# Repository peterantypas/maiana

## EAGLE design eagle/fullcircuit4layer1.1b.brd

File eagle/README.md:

# Eagle CAD files

The new design is a single, 4-layer PCB which does not follow the conventional 4-Layer design paradigm.

- Layer 1 is the component and main signal layer as you might expect.
- Layer 2 is a power and signal layer with no ground pour. The only requirement is that these signals don't cross the RF path anywhere.
- Layer 3 is the ground layer. It is 100% uninterrupted save for via holes. RF traces on Layer 1 form coplanar waveguides with Layer 3 as ground.
- Layer 4 is yet another signal layer with ground pour. Because it lies underneath the ground its traces can go anywhere with no consequences.

By increasing the distance between the signal and ground layer, I was able to use very wide coplanar waveguide traces so as to minimize losses and parasitic inductance.
SWR is better than 1.1:1 with a 50 Ohm load.

The board now requires 7.5 Volts (because of the RF MOSFET). It draws 100 mA while receiving, and spikes to 680 mA during transmission at full power.
Surge current for transmission can be provided by a low-profile 10 mF supercapacitor on the back of the PCB. Also, during transmission,
the external LNA is powered down as a precaution.

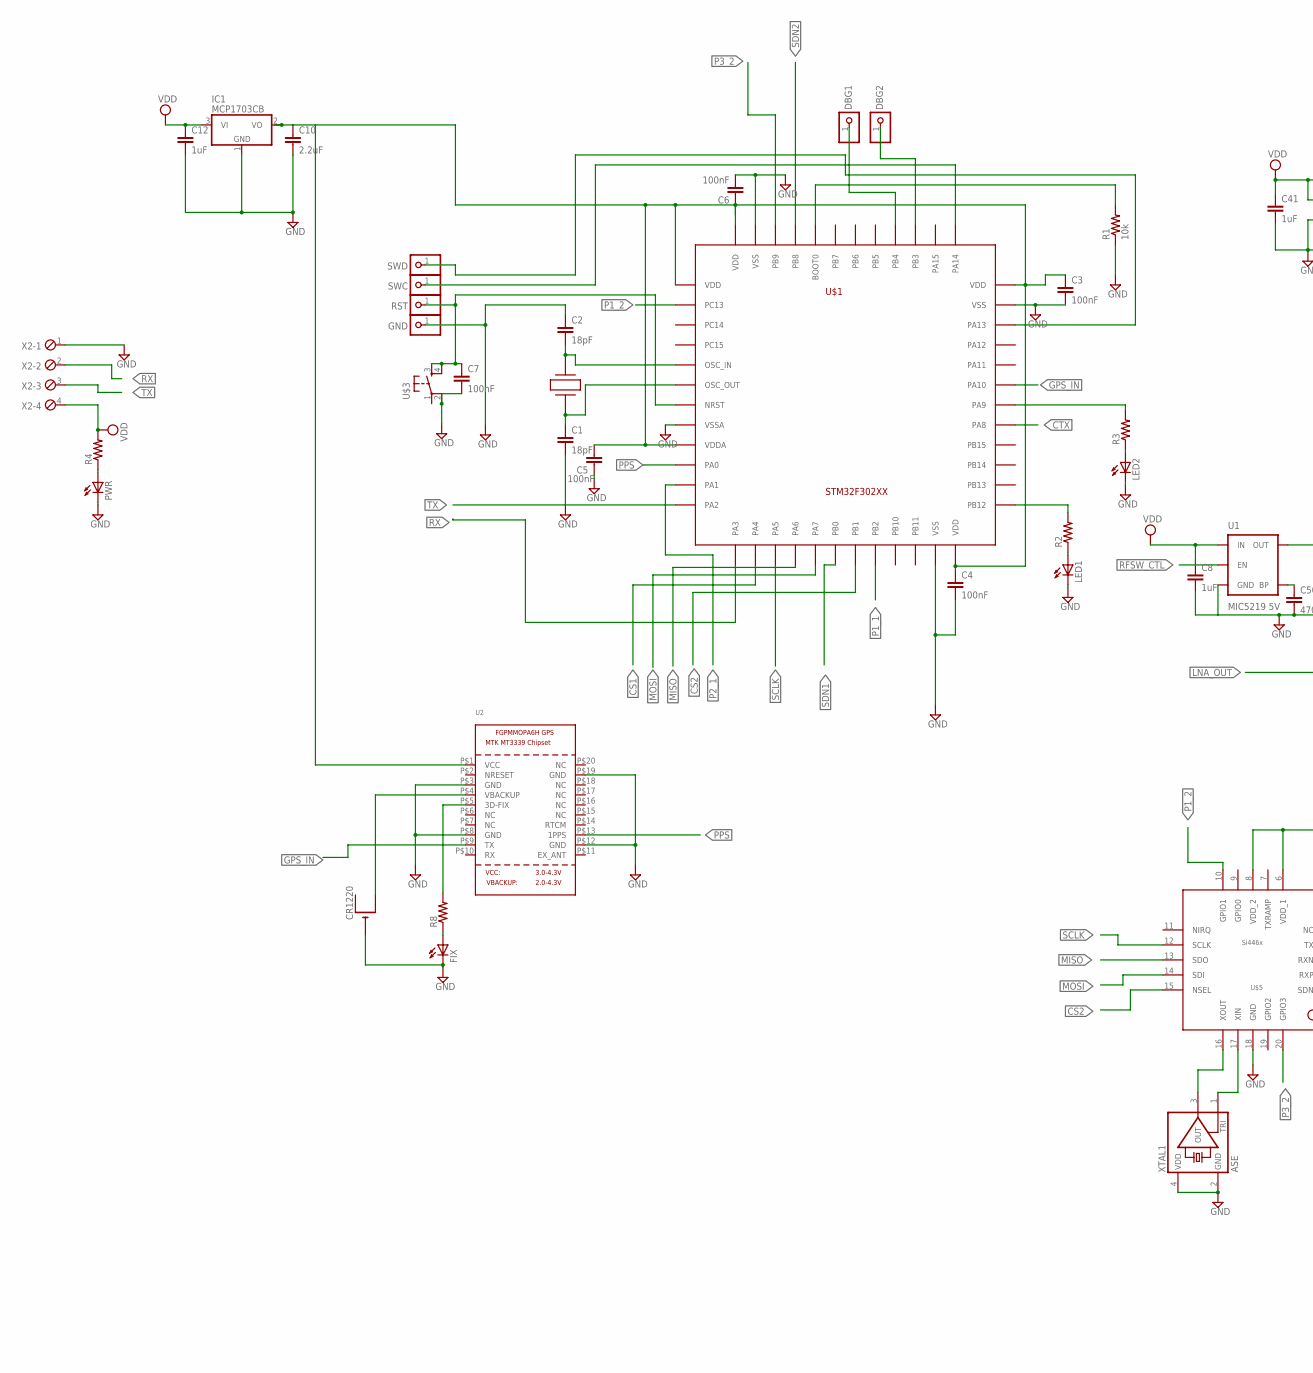
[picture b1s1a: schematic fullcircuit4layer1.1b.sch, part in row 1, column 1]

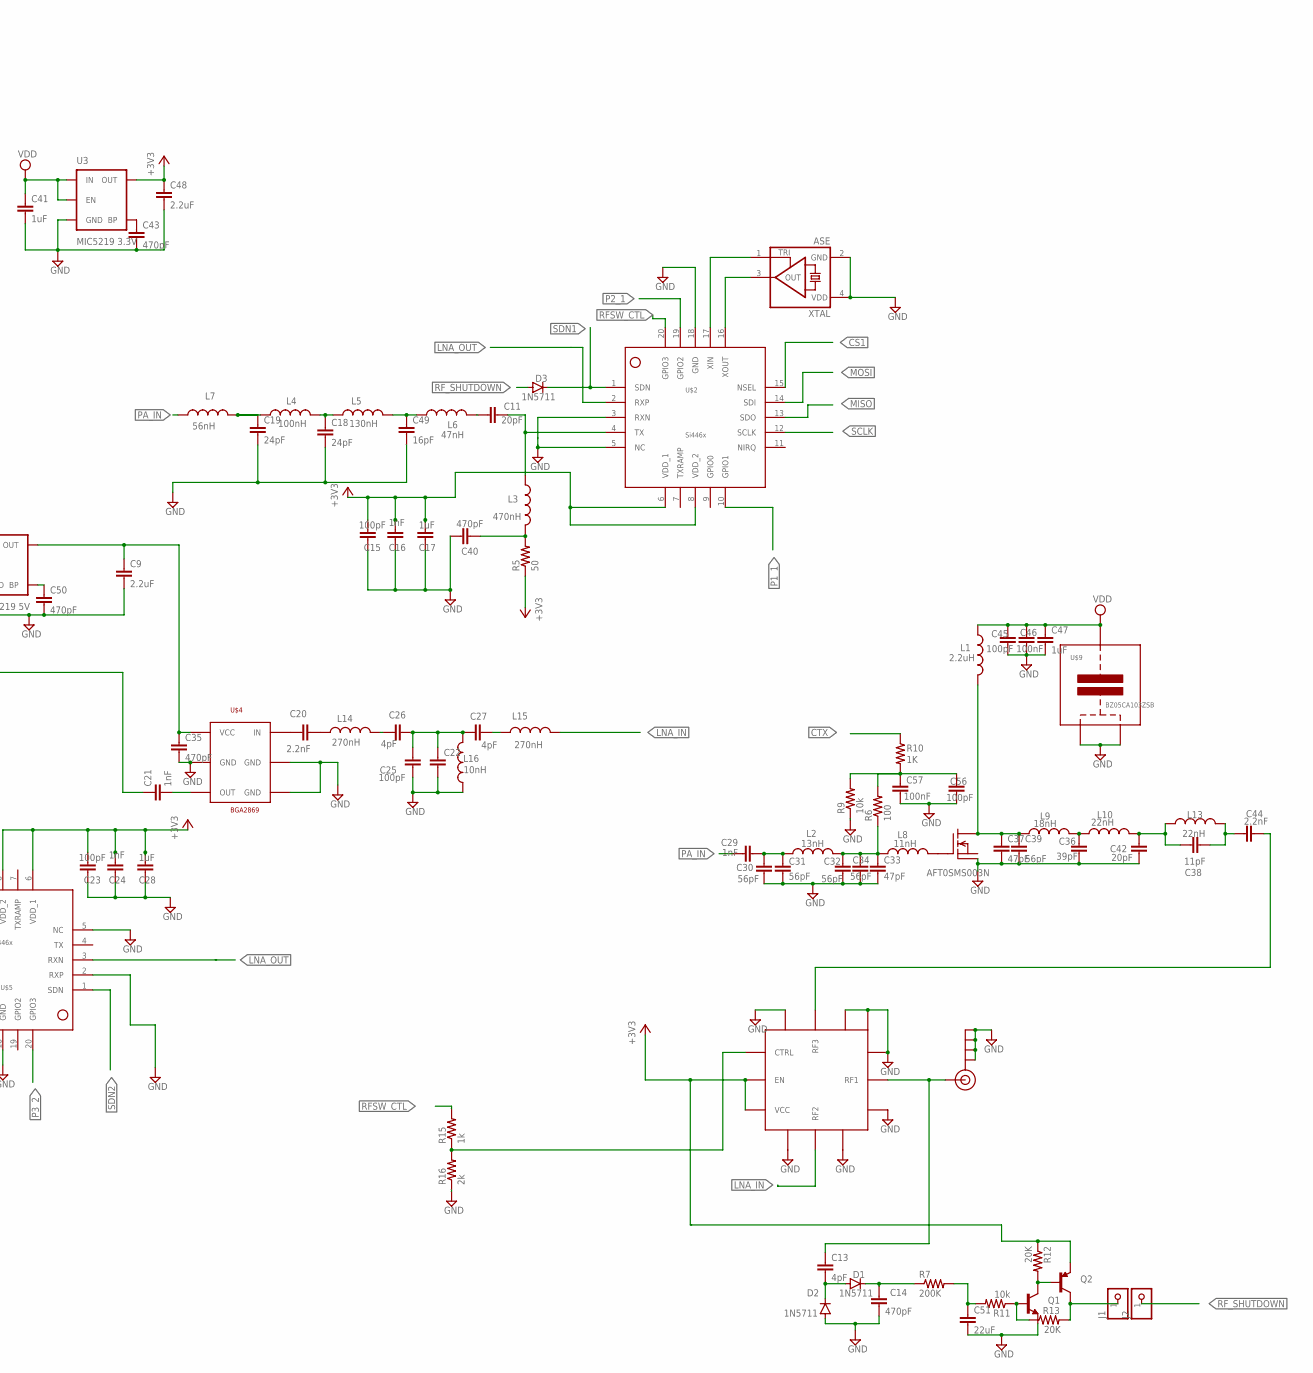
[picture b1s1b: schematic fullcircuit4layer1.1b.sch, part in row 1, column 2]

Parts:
C1, C2: 18pF; 0603-CAP
C3, C4, C5, C6, C7, C57: 100nF; 0603-CAP
C8, C12, C17, C28, C41: 1uF; 0603-CAP
C9, C48: 2.2uF; 0603-CAP
C10: 2.2uF; 0805
C11: 20pF; 0603-CAP
C13, C26, C27: 4pF; 0603-CAP
C14, C35, C40, C43, C50: 470pF; 0603-CAP
C15, C23, C25, C56: 100pF; 0603-CAP
C16, C24: 1nF; 0603-CAP
C18, C19: 24pF; 0603-CAP
C20, C44: 2.2nF; 0805
C21, C29: 1nF; 0805
C22: CAP0603-CAP; 0603-CAP
C30, C31, C32, C34: 56pF; 0603-CAP
C33: 47pF; 0603-CAP
C36: 39pF; 0805
C37: 47pF; 0805
C38: 11pF; 0805
C39: 56pF; 0805
C42: 20pF; 0805
C45: 100pF; 0805
C46: 100nF; 0805
C47: 1uF; 0805
C49: 16pF; 0603-CAP
C51: 22uF; 0805
CR1220: CR1220SMT; CR1220-SMD
D1, D2, D3: 1N5711; SOD-123
DBG1, DBG2: PINHD-1X1; 1X01
FIX: LEDCHIP-LED0603; CHIP-LED0603
GND: PINHD-1X1; 1X01
IC1: MCP1703CB; SOT23
J1, J2: PINHD-1X1; 1X01
J$1: SMA_EDGE; SMA-EDGE
L1: 2.2uH; 0805
L2: 13nH; 0603
L3: 470nH; 0805
L4: 100nH; 0603
L5: 130nH; 0603
L6: 47nH; 0603
L7: 56nH; 0603
L8: 11nH; 0603
L9: 18nH; 0805
L10, L13: 22nH; 0805
L14, L15: 270nH; 0603
L16: 10nH; 0603
LED1, LED2: LEDCHIP-LED0603; CHIP-LED0603
PWR: LEDCHIP-LED0603; CHIP-LED0603
Q1: TRANSISTOR_NPNSOT23-3; SOT23-3
Q2: TRANSISTOR_PNPSMD; SOT23-3
R1, R9, R11: 10k; 0603-RES
R2, R3, R4, R8: RESISTOR0603-RES; 0603-RES
R5: 50; 0603-RES
R6: 100; 0603-RES
R7: 200K; 0603-RES
R10: 1K; 0603-RES
R12, R13: 20K; 0603-RES
R15: 1k; 0603-RES
R16: 2k; 0603-RES
RST: PINHD-1X1; 1X01
SWC: PINHD-1X1; 1X01
SWD: PINHD-1X1; 1X01
U1: MIC5219 5V; SOT23-5
U2: GPS_FGPMMOPA6H; FGPMMOPA6H
U3: MIC5219 3.3V; SOT23-5
U$1: STM32F302XX; LQFP48
U$2, U$5: SI4463
U$3: TACTILE-SWITCH-7914G; 7914G
U$4: BGA2869; SOT363
U$6: SKYWORKS-13330397LF; QFN12
U$7: AFT0SMS003N; SOT-89
U$9: BZ05CA103ZSB; BZ05
X1: TXC_7A
X2: MPT4; 4POL254
XTAL, XTAL1: ASE

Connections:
+3V3: C15.1, C16.1, C17.1, C23.1, C24.1, C28.1, C48.1, Q2.2 (E), R5.1, R12.1, U3.5 (OUT), U$2.6 (VDD_1), U$2.8 (VDD_2), U$5.6 (VDD_1), U$5.8 (VDD_2), U$6.P$8 (EN), U$6.P$9 (VCC)
ANT: C13.1, J$1.SIG (SIGNAL), U$6.P$2 (RF1)
CS1: U$1.P$14 (PA4), U$2.15 (NSEL)
CS2: U$1.P$19 (PB1), U$5.15 (NSEL)
CTX: R10.1, U$1.P$29 (PA8)
GND: C1.2, C2.1, C3.2, C4.2, C5.1, C6.2, C7.2, C8.2, C9.2, C10.2, C12.2, C14.2, C15.2, C16.2, C17.2, C18.2, C19.2, C22.2, C23.2, C24.2, C25.1, C28.2, C30.2, C31.2, C32.2, C33.2, C34.2, C35.2, C36.2, C37.2, C39.2, C40.2, C41.2, C42.2, C43.2, C45.2, C46.2, C47.2, C48.2, C49.2, C50.2, C51.2, C56.2, C57.2, CR1220.-, D2.A, FIX.C, GND.1, IC1.1 (GND), J$1.GND@0 (GND), J$1.GND@1 (GND), J$1.GND@2 (GND), J$1.GND@3 (GND), L16.1, LED1.C, LED2.C, PWR.C, Q1.2 (E), R1.1, R9.1, R16.1, U1.2 (GND), U2.P$3 (GND), U2.P$8 (GND), U2.P$12 (GND), U2.P$19 (GND), U3.2 (GND), U$1.P$8 (VSSA), U$1.P$23 (VSS), U$1.P$35 (VSS), U$1.P$47 (VSS), U$2.3 (RXN), U$2.5 (NC), U$2.18 (GND), U$3.2, U$4.2 (GND), U$4.4 (GND), U$4.5 (GND), U$5.2 (RXP), U$5.5 (NC), U$5.18 (GND), U$6.P$1 (GND), U$6.P$3 (GND), U$6.P$4 (GND), U$6.P$6 (GND), U$6.P$10 (GND), U$6.P$12 (GND), U$7.2@1 (PAD), U$9.P$1, U$9.P$2, X2.1, XTAL.2 (GND), XTAL.4 (VDD), XTAL1.2 (GND), XTAL1.4 (VDD)
GPS_IN: U2.P$9 (TX), U$1.P$31 (PA10)
LNAPWR: C9.1, C35.1, U1.5 (OUT), U$4.1 (VCC)
LNA_IN: L15.2, U$6.P$11 (RF2)
LNA_OUT: C21.1, U$2.2 (RXP), U$5.3 (RXN)
MISO: U$1.P$16 (PA6), U$2.13 (SDO), U$5.13 (SDO)
MOSI: U$1.P$17 (PA7), U$2.14 (SDI), U$5.14 (SDI)
unnamed: U$2.17 (XIN), XTAL.1 (TRI)
unnamed: C19.1, L4.1, L7.2
unnamed: C18.1, L4.2, L5.1
unnamed: R1.2, U$1.P$44 (BOOT0)
unnamed: SWC.1, U$1.P$37 (PA14)
unnamed: R2.2, U$1.P$25 (PB12)
unnamed: SWD.1, U$1.P$34 (PA13)
unnamed: C11.1, L3.1, U$2.4 (TX)
unnamed: C2.2, U$1.P$5 (OSC_IN), X1.P$2
unnamed: C20.1, U$4.6 (IN)
unnamed: C21.2, U$4.3 (OUT)
unnamed: FIX.A, R8.1
unnamed: U$2.16 (XOUT), XTAL.3 (OUT)
unnamed: LED1.A, R2.1
unnamed: C20.2, L14.1
unnamed: LED2.A, R3.1
unnamed: R3.2, U$1.P$30 (PA9)
unnamed: C1.1, U$1.P$6 (OSC_OUT), X1.P$1
unnamed: PWR.A, R4.1
unnamed: C49.1, L5.2, L6.1
unnamed: DBG2.1, U$1.P$39 (PB3)
unnamed: C3.1, C4.1, C5.2, C6.1, C10.1, IC1.2 (VO), U2.P$1 (VCC), U$1.P$1 (VDD), U$1.P$9 (VDDA), U$1.P$24 (VDD), U$1.P$36 (VDD), U$1.P$48 (VDD)
unnamed: C37.1, C39.1, L1.2, L9.1, U$7.3 (D)
unnamed: DBG1.1, U$1.P$40 (PB4)
unnamed: L8.2, U$7.1 (G)
unnamed: C32.1, C33.1, C34.1, L2.2, L8.1, R6.1
unnamed: C29.2, C30.1, C31.1, L2.1
unnamed: C36.1, L9.2, L10.1
unnamed: C38.1, C42.1, L10.2, L13.1
unnamed: R8.2, U2.P$5 (3D-FIX)
unnamed: C43.1, U3.4 (BP)
unnamed: C13.2, D1.A, D2.C
unnamed: CR1220.+$2 (+1), U2.P$4 (VBACKUP)
unnamed: C22.1, C25.2, C26.1, C27.2, L16.2
unnamed: C27.1, L15.1
unnamed: C26.2, L14.2
unnamed: C50.1, U1.4 (BP)
unnamed: U$5.17 (XIN), XTAL1.1 (TRI)
unnamed: U$5.16 (XOUT), XTAL1.3 (OUT)
unnamed: C14.1, D1.C, R7.1
unnamed: Q1.3 (C), Q2.1 (B), R12.2
unnamed: Q1.1 (B), R11.1, R13.1
unnamed: C38.2, C44.1, L13.2
unnamed: C51.1, R7.2, R11.2
unnamed: C11.2, L6.2
unnamed: C40.1, L3.2, R5.2
unnamed: C56.1, C57.1, R6.2, R9.2, R10.2
unnamed: C7.1, RST.1, U$1.P$7 (NRST), U$3.3, U$3.4
P1_1: U$1.P$20 (PB2), U$2.10 (GPIO1)
P1_2: U$1.P$2 (PC13), U$5.10 (GPIO1)
P2_1: U$1.P$11 (PA1), U$2.19 (GPIO2)
P3_2: U$1.P$46 (PB9), U$5.20 (GPIO3)
PA_IN: C29.1, L7.1
PA_OUT: C44.2, U$6.P$5 (RF3)
PPS: U2.P$13 (1PPS), U$1.P$10 (PA0)
RFSWCTL: R15.1, R16.2, U$6.P$7 (CTRL)
RFSW_CTL: R15.2, U1.3 (EN), U$2.20 (GPIO3)
RF_DETECT_LOGIC: J1.1, Q2.3 (C), R13.2
RF_SHUTDOWN: D3.A, J2.1
RX: U$1.P$13 (PA3), X2.2
SCLK: U$1.P$15 (PA5), U$2.12 (SCLK), U$5.12 (SCLK)
SDN1: D3.C, U$1.P$18 (PB0), U$2.1 (SDN)
SDN2: U$1.P$45 (PB8), U$5.1 (SDN)
TX: U$1.P$12 (PA2), X2.3
VDD: C8.1, C12.1, C41.1, C45.1, C46.1, C47.1, IC1.3 (VI), L1.1, R4.2, U1.1 (IN), U3.1 (IN), U3.3 (EN), U$9.P$3, X2.4

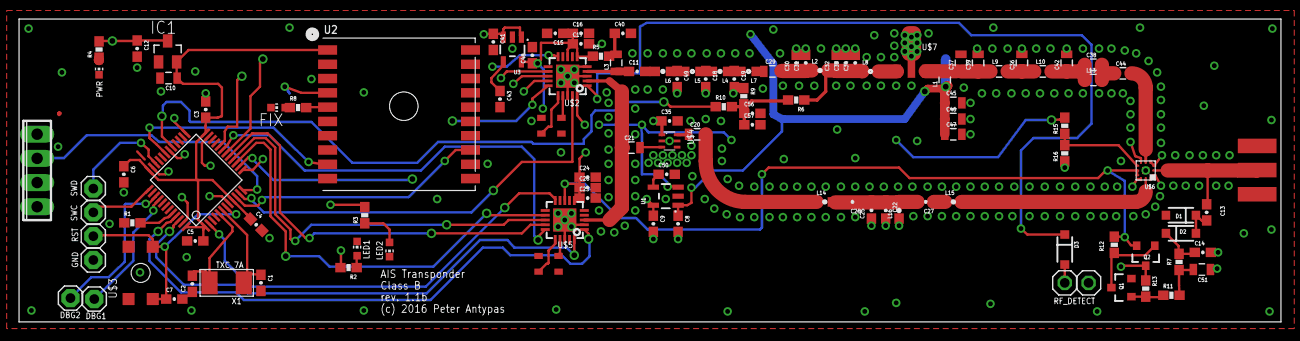
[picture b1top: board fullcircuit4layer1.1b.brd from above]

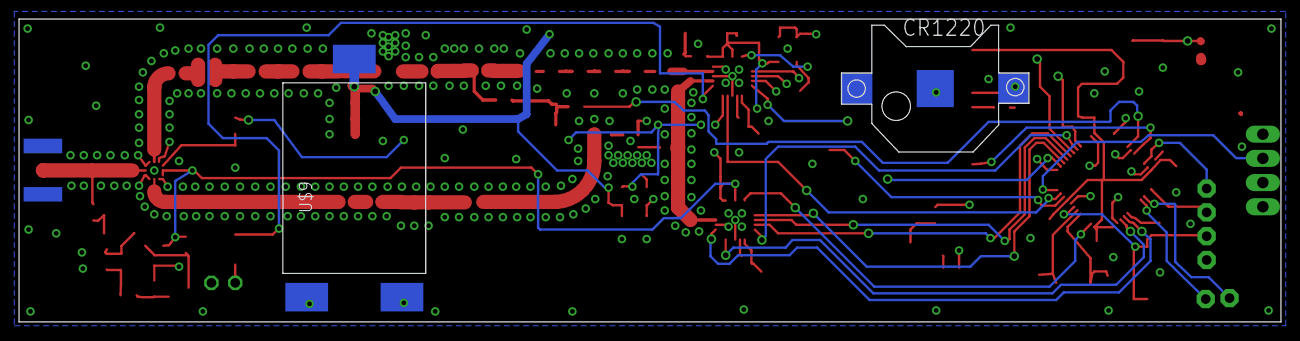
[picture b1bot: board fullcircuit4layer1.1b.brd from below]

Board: 4 copper layers, 132.5 x 31.8 mm, 117 parts (2 on the bottom side), 77 nets.

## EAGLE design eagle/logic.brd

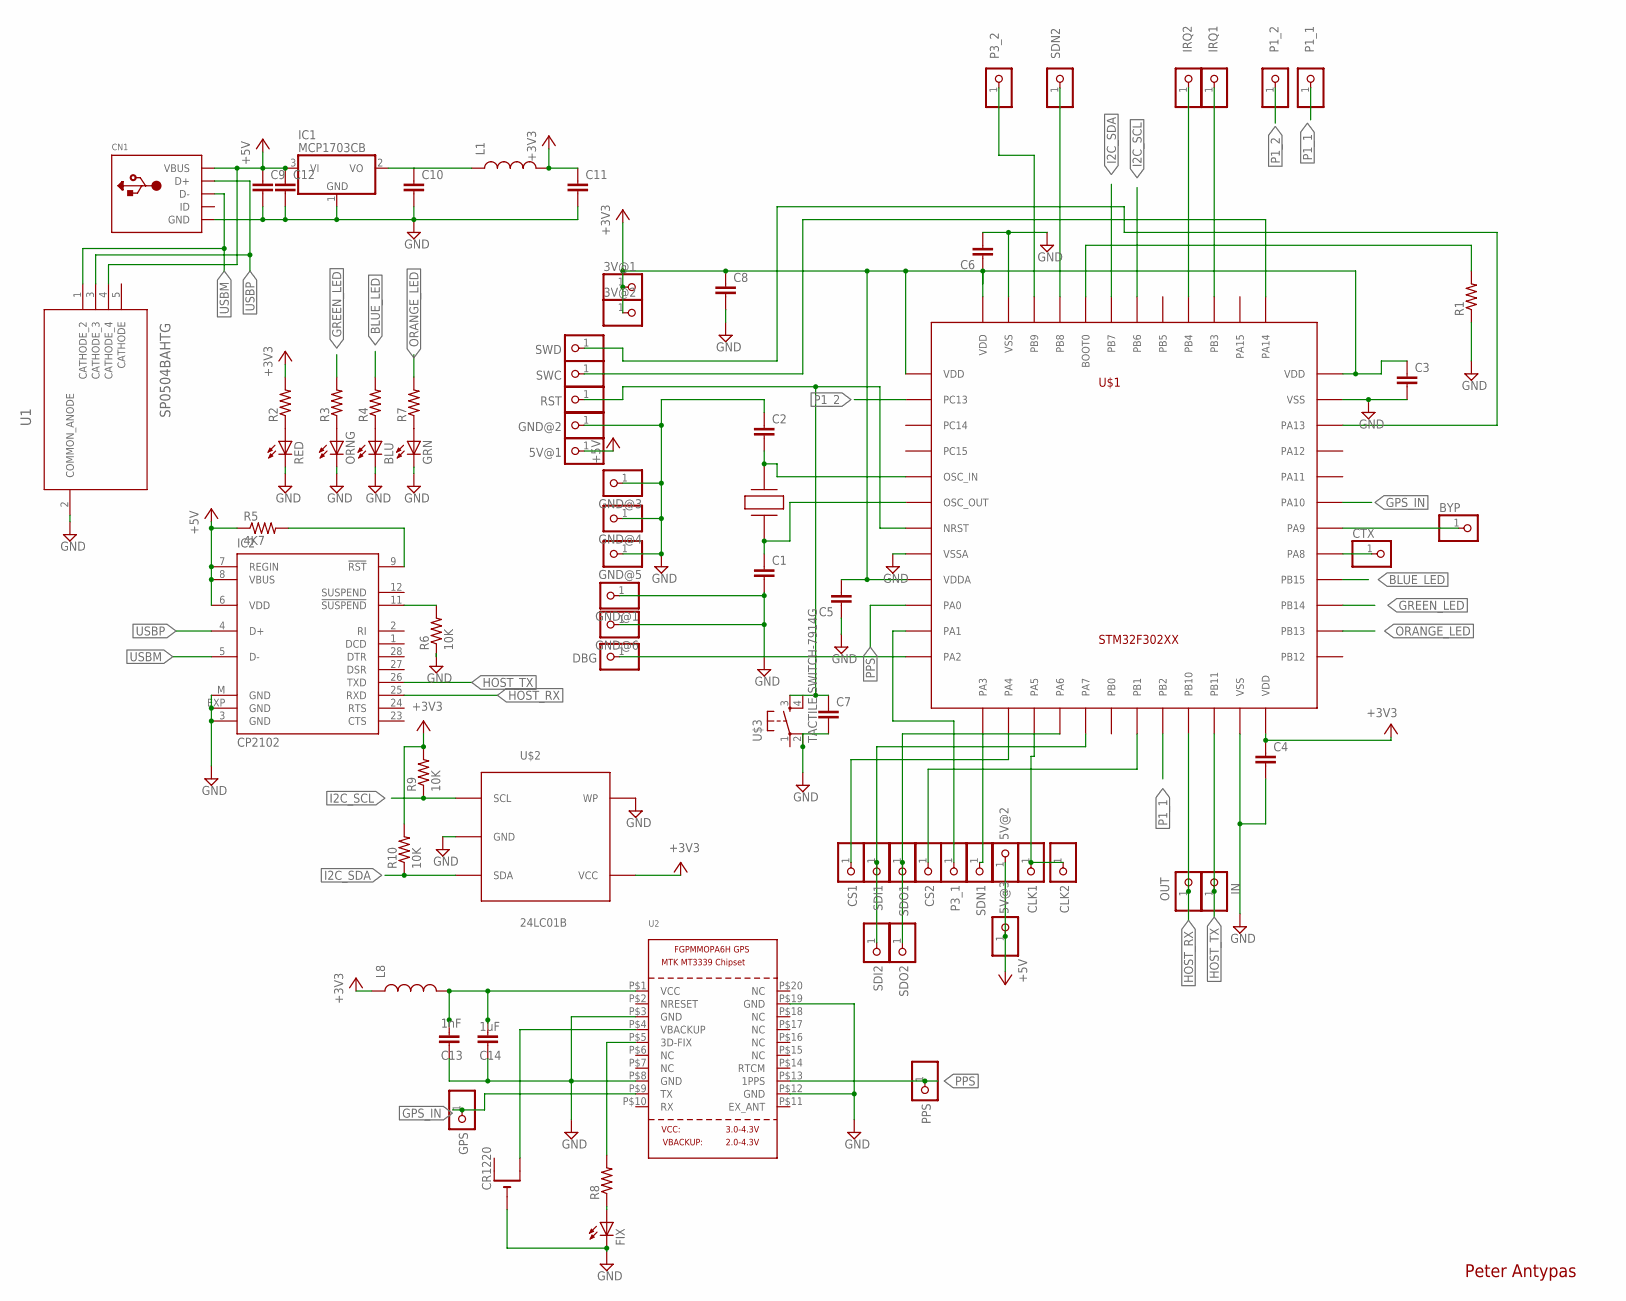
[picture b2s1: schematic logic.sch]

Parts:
3V@1, 3V@2, 5V@1, 5V@2, 5V@3: PINHD-1X1; 1X01
BLU: LEDCHIP-LED0603; CHIP-LED0603
BYP: PINHD-1X1; 1X01
C1, C2, C3, C4, C5, C6, C7, C8, C11, C12: CAP0603-CAP; 0603-CAP
C9, C10: CAP0805; 0805
C13: 1nF; 0603-CAP
C14: 1uF; 0603-CAP
CLK1, CLK2: PINHD-1X1; 1X01
CN1: USBMINIB; USB-MINIB
CR1220: CR1220SMT; CR1220-SMD
CS1, CS2: PINHD-1X1; 1X01
CTX: PINHD-1X1; 1X01
DBG: PINHD-1X1; 1X01
FIX: LEDCHIP-LED0603; CHIP-LED0603
GND@1, GND@2, GND@3, GND@4, GND@5, GND@6: PINHD-1X1; 1X01
GPS: PINHD-1X1; 1X01
GRN: LEDCHIP-LED0603; CHIP-LED0603
IC1: MCP1703CB; SOT23
IC2: CP2102; MLP28
IN: PINHD-1X1; 1X01
IRQ1, IRQ2: PINHD-1X1; 1X01
L1: INDUCTOR30OHM,1.8A; 0603
L8: INDUCTOR0603; 0603
ORNG: LEDCHIP-LED0603; CHIP-LED0603
OUT: PINHD-1X1; 1X01
P1_1, P1_2, P3_1, P3_2: PINHD-1X1; 1X01
PPS: PINHD-1X1; 1X01
R1, R2, R3, R4, R7, R8: RESISTOR0603-RES; 0603-RES
R5: 4K7; 0603-RES
R6, R9, R10: 10K; 0603-RES
RED: LEDCHIP-LED0603; CHIP-LED0603
RST: PINHD-1X1; 1X01
SDI1, SDI2: PINHD-1X1; 1X01
SDN1, SDN2: PINHD-1X1; 1X01
SDO1, SDO2: PINHD-1X1; 1X01
SWC: PINHD-1X1; 1X01
SWD: PINHD-1X1; 1X01
U1: SP0504BAHTG; SOT95P280X145-5N
U2: GPS_FGPMMOPA6H; FGPMMOPA6H
U$1: STM32F302XX; LQFP48
U$2: 24LC01B; SOT23-5
U$3: TACTILE-SWITCH-7914G; 7914G
X1: TXC_7A

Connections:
+3V3: 3V@1.1, 3V@2.1, C3.1, C4.1, C5.2, C6.1, C8.1, C11.1, L1.2, L8.1, R2.2, R9.2, R10.2, U$1.P$1 (VDD), U$1.P$9 (VDDA), U$1.P$24 (VDD), U$1.P$36 (VDD), U$1.P$48 (VDD), U$2.4 (VCC)
+5V: 5V@1.1, 5V@2.1, 5V@3.1, C9.1, C12.1, CN1.VBUS, IC1.3 (VI), IC2.6 (VDD), IC2.7 (REGIN), IC2.8 (VBUS), R5.1, U1.4 (CATHODE_4)
BLUE_LED: R4.2, U$1.P$28 (PB15)
EEPROM_CS: C7.1, RST.1, U$1.P$7 (NRST), U$3.3
GND: BLU.C, C1.2, C2.1, C3.2, C4.2, C5.1, C6.2, C7.2, C8.2, C9.2, C10.2, C11.2, C12.2, C13.2, C14.2, CN1.GND, CR1220.-, FIX.C, GND@1.1, GND@2.1, GND@3.1, GND@4.1, GND@5.1, GND@6.1, GRN.C, IC1.1 (GND), IC2.3 (GND), IC2.EXP (GND), IC2.M (GND), ORNG.C, R1.1, R6.1, U1.2 (COMMON_ANODE), U2.P$3 (GND), U2.P$8 (GND), U2.P$12 (GND), U2.P$19 (GND), U$1.P$8 (VSSA), U$1.P$23 (VSS), U$1.P$35 (VSS), U$1.P$47 (VSS), U$2.2 (GND), U$2.5 (WP), U$3.2
GPS_IN: GPS.1, U2.P$9 (TX), U$1.P$31 (PA10)
GREEN_LED: R3.2, U$1.P$27 (PB14)
HOST_RX: IC2.25 (RXD), OUT.1, U$1.P$21 (PB10)
HOST_TX: IC2.26 (TXD), IN.1, U$1.P$22 (PB11)
I2C_SCL: R9.1, U$1.P$42 (PB6), U$2.1 (SCL)
I2C_SDA: R10.1, U$1.P$43 (PB7), U$2.3 (SDA)
unnamed: SDN2.1, U$1.P$45 (PB8)
unnamed: P3_1.1, U$1.P$11 (PA1)
unnamed: C10.1, IC1.2 (VO), L1.1
unnamed: R1.2, U$1.P$44 (BOOT0)
unnamed: SWC.1, U$1.P$37 (PA14)
unnamed: SDN1.1, U$1.P$13 (PA3)
unnamed: SWD.1, U$1.P$34 (PA13)
unnamed: IRQ1.1, U$1.P$39 (PB3)
unnamed: C2.2, U$1.P$5 (OSC_IN), X1.P$2
unnamed: CS1.1, U$1.P$14 (PA4)
unnamed: IRQ2.1, U$1.P$40 (PB4)
unnamed: FIX.A, R8.1
unnamed: CS2.1, U$1.P$19 (PB1)
unnamed: DBG.1, U$1.P$12 (PA2)
unnamed: P3_2.1, U$1.P$46 (PB9)
unnamed: R2.1, RED.A
unnamed: ORNG.A, R3.1
unnamed: C1.1, U$1.P$6 (OSC_OUT), X1.P$1
unnamed: BLU.A, R4.1
unnamed: CTX.1, U$1.P$29 (PA8)
unnamed: IC2.9 (!RST), R5.2
unnamed: IC2.11 (!SUSPEND), R6.2
unnamed: GRN.A, R7.1
unnamed: BYP.1, U$1.P$30 (PA9)
unnamed: R8.2, U2.P$5 (3D-FIX)
unnamed: CR1220.+$2 (+1), U2.P$4 (VBACKUP)
ORANGE_LED: R7.2, U$1.P$26 (PB13)
P1_1: P1_1.1, U$1.P$20 (PB2)
P1_2: P1_2.1, U$1.P$2 (PC13)
PPS: PPS.1, U2.P$13 (1PPS), U$1.P$10 (PA0)
PWR: RED.C
SDI: SDI1.1, SDI2.1, U$1.P$17 (PA7)
SDO: SDO1.1, SDO2.1, U$1.P$16 (PA6)
SPI_CLK: CLK1.1, CLK2.1, U$1.P$15 (PA5)
USBM: CN1.D-, IC2.5 (D-), U1.1 (CATHODE_2)
USBP: CN1.D+, IC2.4 (D+), U1.3 (CATHODE_3)
VDD1: C13.1, C14.1, L8.2, U2.P$1 (VCC)

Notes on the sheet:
Peter Antypas

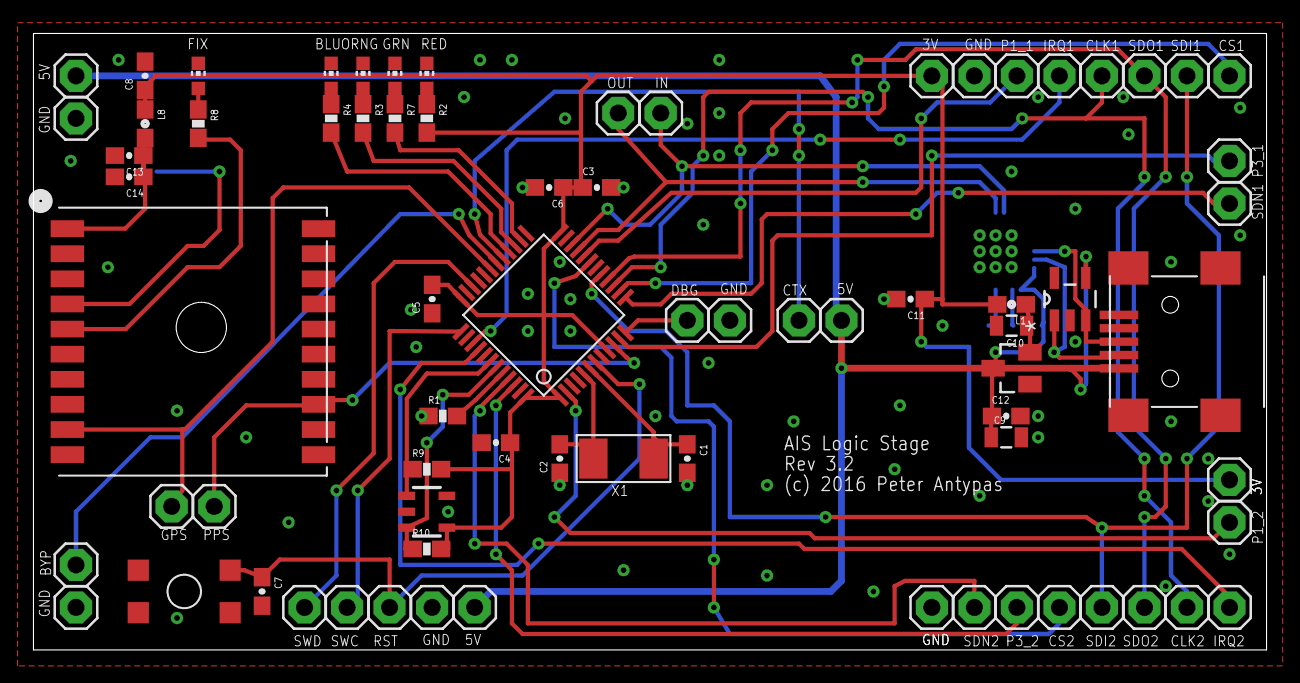
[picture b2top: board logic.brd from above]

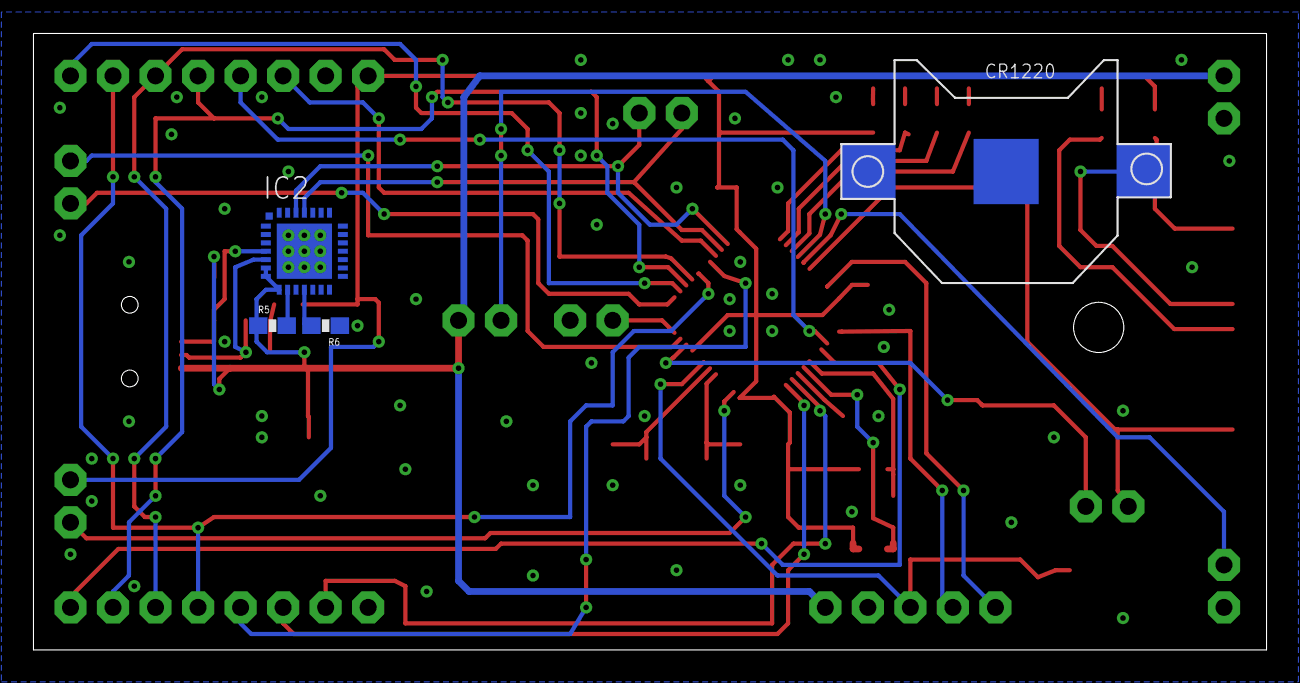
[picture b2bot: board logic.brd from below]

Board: 2 copper layers, 73.6 x 36.8 mm, 78 parts (4 on the bottom side), 47 nets.

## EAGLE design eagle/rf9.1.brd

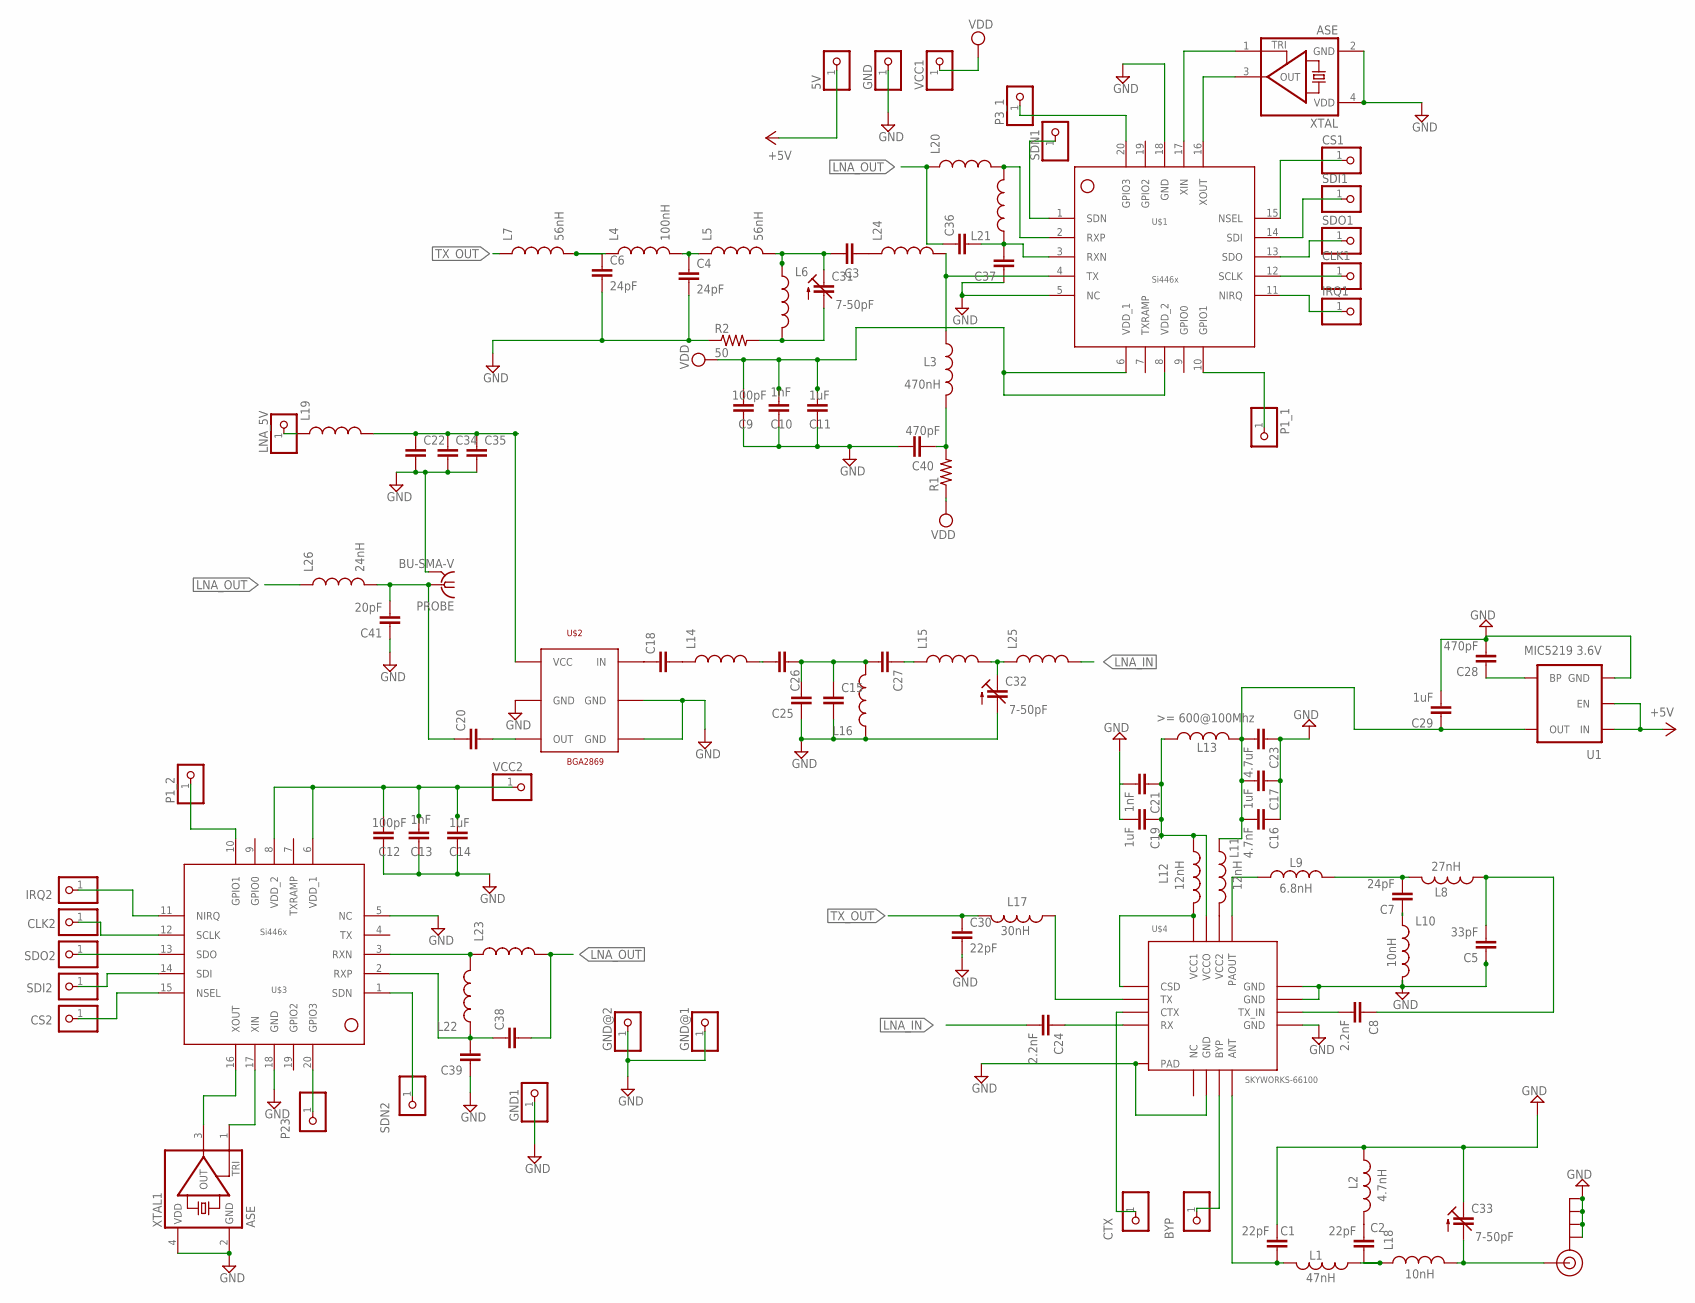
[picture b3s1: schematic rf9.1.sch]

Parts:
5V: PINHD-1X1; 1X01
BYP: PINHD-1X1; 1X01
C1, C2, C30: 22pF; 0603-CAP
C3, C15, C22, C25, C26, C27, C34, C35, C36, C37, C38, C39: CAP0603-CAP; 0603-CAP
C4, C6, C7: 24pF; 0603-CAP
C5: 33pF; 0603-CAP
C8: 2.2nF; 0603-CAP
C9, C12: 100pF; 0603-CAP
C10, C13: 1nF; 0603-CAP
C11, C14: 1uF; 0603-CAP
C16: 4.7nF; 0805
C17, C19, C29: 1uF; 0805
C18, C20: CAP0805; 0805
C21: 1nF; 0805
C23: 4.7uF; 0805
C24: 2.2nF; 0805
C28, C40: 470pF; 0603-CAP
C31, C32, C33: 7-50pF; CTRIMTZBX4
C41: 20pF; 0603-CAP
CLK1, CLK2: PINHD-1X1; 1X01
CS1, CS2: PINHD-1X1; 1X01
CTX: PINHD-1X1; 1X01
GND, GND1: PINHD-1X1; 1X01
GND@1, GND@2: PINHD-1X1; 1X01
IRQ1, IRQ2: PINHD-1X1; 1X01
J$1: SMA_EDGE; SMA-EDGE
L1: 47nH; 0603
L2: 4.7nH; 0603
L3: 470nH; 0805
L4: 100nH; 0603
L5, L7: 56nH; 0603
L6, L14, L15, L16, L19, L20, L21, L22, L23, L24, L25: INDUCTOR30OHM,1.8A; 0603
L8: 27nH; 0603
L9: 6.8nH; 0603
L10, L18: 10nH; 0603
L11, L12: 12nH; 0603
L13: >= 600@100Mhz; 0603
L17: 30nH; 0603
L26: 24nH; 0603
LNA_5V: PINHD-1X1; 1X01
P1_1, P1_2, P3_1, P23: PINHD-1X1; 1X01
PROBE: BU-SMA-V
R1: RESISTOR0603-RES; 0603-RES
R2: 50; 0603-RES
SDI1, SDI2: PINHD-1X1; 1X01
SDN1, SDN2: PINHD-1X1; 1X01
SDO1, SDO2: PINHD-1X1; 1X01
U1: MIC5219 3.6V; SOT23-5
U$1, U$3: SI4463
U$2: BGA2869; SOT363
U$4: SKYWORKS-66100; MCM16
VCC1, VCC2: PINHD-1X1; 1X01
XTAL, XTAL1: ASE

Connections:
+5V: 5V.1, U1.1 (IN), U1.3 (EN)
CS: CS1.1, U$1.15 (NSEL)
GND: C1.2, C4.2, C5.1, C6.2, C9.2, C10.2, C11.2, C12.2, C13.2, C14.2, C15.2, C16.1, C17.1, C19.2, C21.2, C22.2, C23.1, C25.1, C28.2, C29.2, C30.2, C32.2 (A), C33.1 (E), C34.2, C35.2, C37.1, C39.1, C40.2, C41.1, GND.1, GND1.1, GND@1.1, GND@2.1, J$1.GND@0 (GND), J$1.GND@1 (GND), J$1.GND@2 (GND), J$1.GND@3 (GND), L2.1, L10.2, L16.1, PROBE.2, PROBE.3 (2), PROBE.4 (2), PROBE.5 (2), R2.1, U1.2 (GND), U$1.5 (NC), U$1.18 (GND), U$2.2 (GND), U$2.4 (GND), U$2.5 (GND), U$3.5 (NC), U$3.18 (GND), U$4.P$6 (GND), U$4.P$9 (GND), U$4.P$11 (GND), U$4.P$12 (GND), U$4.P$17 (PAD), XTAL.2 (GND), XTAL.4 (VDD), XTAL1.2 (GND), XTAL1.4 (VDD)
IRQ2: IRQ2.1, U$3.11 (NIRQ)
LNA_5V: C22.1, C34.1, C35.1, L19.2, U$2.1 (VCC)
LNA_IN: C24.2, L25.2
LNA_OUT: C36.1, C38.2, L20.1, L23.2, L26.1
unnamed: C2.1, L1.1, L18.1
unnamed: C1.1, L1.2, U$4.P$8 (ANT)
unnamed: C4.1, L4.2, L5.1
unnamed: C6.1, L4.1, L7.2
unnamed: P23.1, U$3.20 (GPIO3)
unnamed: L3.1, L24.2, U$1.4 (TX)
unnamed: U$1.17 (XIN), XTAL.1 (TRI)
unnamed: C2.2, L2.2
unnamed: C8.2, U$4.P$10 (TX_IN)
unnamed: P1_2.1, U$3.10 (GPIO1)
unnamed: C5.2, C8.1, L8.1
unnamed: C7.2, L8.2, L9.2
unnamed: U$1.16 (XOUT), XTAL.3 (OUT)
unnamed: C18.1, U$2.6 (IN)
unnamed: C18.2, L14.1
unnamed: C20.2, U$2.3 (OUT)
unnamed: C7.1, L10.1
unnamed: C31.2 (A), L6.2, R2.2
unnamed: L9.1, U$4.P$13 (PAOUT)
unnamed: C3.2, C31.1 (E), L5.2, L6.1
unnamed: C19.1, C21.1, L12.1, L13.1, U$4.P$15 (VCCO)
unnamed: L12.2, U$4.P$1 (CSD), U$4.P$16 (VCC1)
unnamed: C24.1, U$4.P$4 (RX)
unnamed: IRQ1.1, U$1.11 (NIRQ)
unnamed: BYP.1, U$4.P$7 (BYP)
unnamed: CTX.1, U$4.P$3 (CTX)
unnamed: C28.1, U1.4 (BP)
unnamed: C16.2, C17.2, C23.2, C29.1, L11.1, L13.2, U1.5 (OUT)
unnamed: SDI2.1, U$3.14 (SDI)
unnamed: CS2.1, U$3.15 (NSEL)
unnamed: L11.2, U$4.P$14 (VCC2)
unnamed: C15.1, C25.2, C26.1, C27.2, L16.2
unnamed: C27.1, L15.1
unnamed: C26.2, L14.2
unnamed: SDN1.1, U$1.1 (SDN)
unnamed: U$3.17 (XIN), XTAL1.1 (TRI)
unnamed: U$3.16 (XOUT), XTAL1.3 (OUT)
unnamed: SDN2.1, U$3.1 (SDN)
unnamed: SDO2.1, U$3.13 (SDO)
unnamed: L17.1, U$4.P$2 (TX)
unnamed: C33.2 (A), J$1.SIG (SIGNAL), L18.2
unnamed: CLK2.1, U$3.12 (SCLK)
unnamed: L19.1, LNA_5V.1
unnamed: L20.2, L21.2, U$1.2 (RXP)
unnamed: L22.2, L23.1, U$3.3 (RXN)
unnamed: C38.1, C39.2, L22.1, U$3.2 (RXP)
unnamed: C36.2, C37.2, L21.1, U$1.3 (RXN)
unnamed: C40.1, L3.2, R1.2
unnamed: C3.1, L24.1
unnamed: C32.1 (E), L15.2, L25.1
unnamed: C20.1, C41.2, L26.2, PROBE.1
SCLK: CLK1.1, U$1.12 (SCLK)
SCLK2: P1_1.1, U$1.10 (GPIO1)
SCLK3: P3_1.1, U$1.20 (GPIO3)
SDI: SDI1.1, U$1.14 (SDI)
SDO: SDO1.1, U$1.13 (SDO)
TX_OUT: C30.1, L7.1, L17.2
VCC2: C12.1, C13.1, C14.1, U$3.6 (VDD_1), U$3.8 (VDD_2), VCC2.1
VDD: C9.1, C10.1, C11.1, R1.1, U$1.6 (VDD_1), U$1.8 (VDD_2), VCC1.1

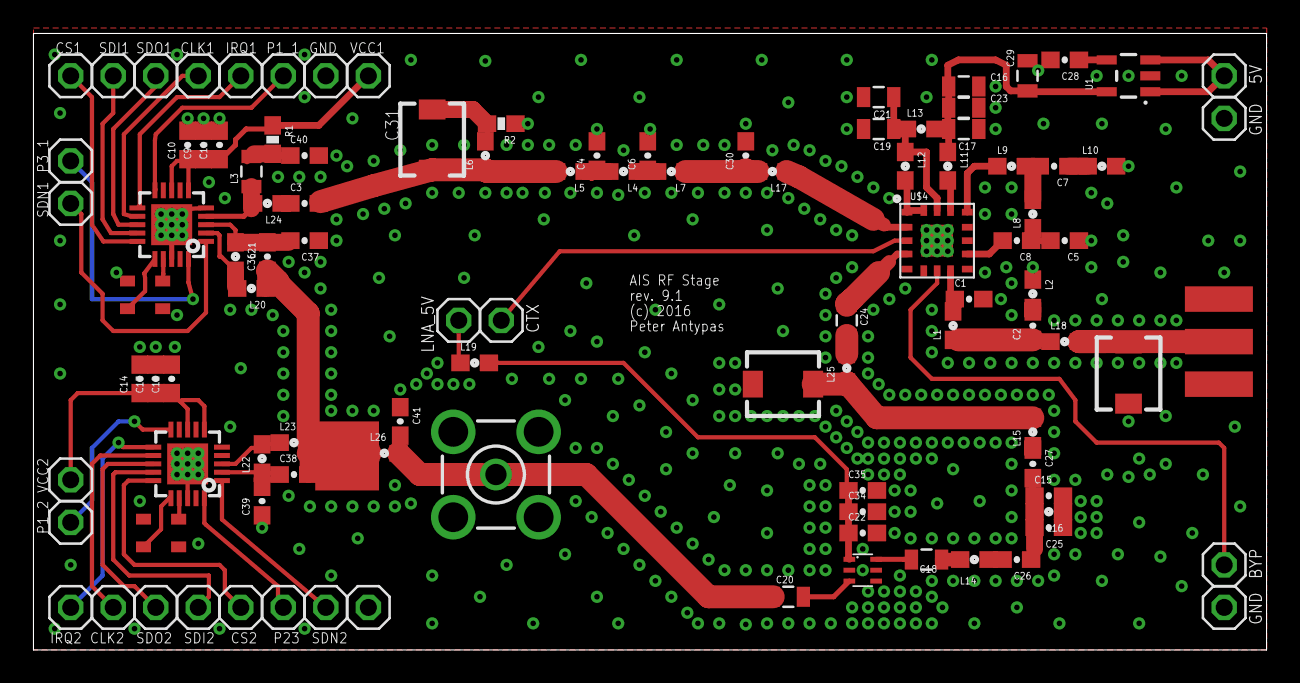
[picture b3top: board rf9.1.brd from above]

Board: 2 copper layers, 73.6 x 36.8 mm, 104 parts (0 on the bottom side), 66 nets.

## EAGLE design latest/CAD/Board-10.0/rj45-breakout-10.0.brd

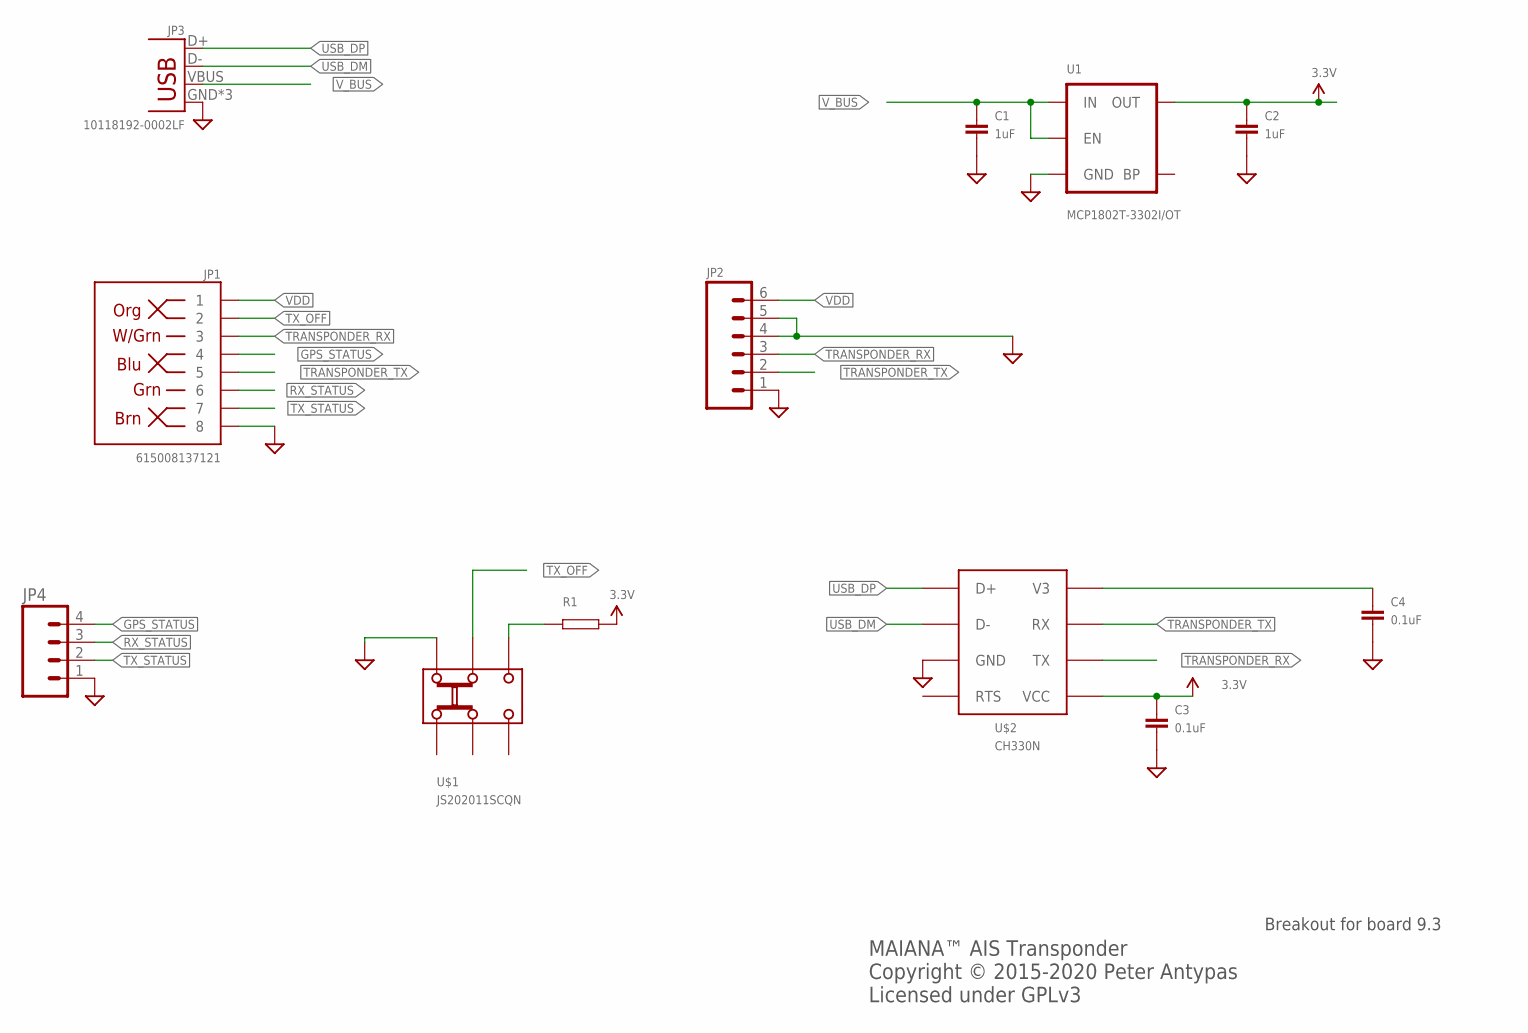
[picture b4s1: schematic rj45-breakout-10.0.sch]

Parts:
C1, C2: 1uF; 0603
C3, C4: 0.1uF; 0603
JP1: 615008137121; RJ45-8
JP2: M06SILK_FEMALE_PTH; 1X06
JP3: 10118192-0002LF; USB-MICROB
JP4: M04PTH; 1X04
R1: RESISTOR0603; 0603
U1: MCP1802T-3302I/OT; SOT23-5
U$1: JS202011SCQN; DPDT-SMD
U$2: CH330N; SOIC-8

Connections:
3.3V: C2.P$1 (1), C3.P$1 (1), R1.P$2, U1.5 (OUT), U$2.5 (VCC)
GND: C1.P$2 (2), C2.P$2 (2), C3.P$2 (2), C4.P$2 (2), JP1.8, JP2.1, JP2.4, JP2.5, JP3.GND, JP3.MT1 (GND), JP3.MT2 (GND), JP4.1, U1.2 (GND), U$1.P$6, U$2.3 (GND)
GPS_STATUS: JP1.4, JP4.4
unnamed: C4.P$1 (1), U$2.8 (V3)
unnamed: R1.P$1, U$1.P$4
RX_STATUS: JP1.6, JP4.3
TRANSPONDER_RX: JP1.3, JP2.3, U$2.6 (TX)
TRANSPONDER_TX: JP1.5, JP2.2, U$2.7 (RX)
TX_OFF: JP1.2, U$1.P$5
TX_STATUS: JP1.7, JP4.2
USB_DM: JP3.D-, U$2.2 (D-)
USB_DP: JP3.D+, U$2.1 (D+)
VDD: JP1.1, JP2.6
V_BUS: C1.P$1 (1), JP3.VBUS, U1.1 (IN), U1.3 (EN)

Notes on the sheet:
MAIANA™ AIS Transponder Copyright © 2015-2020 Peter Antypas Licensed under GPLv3
Breakout for board 9.3

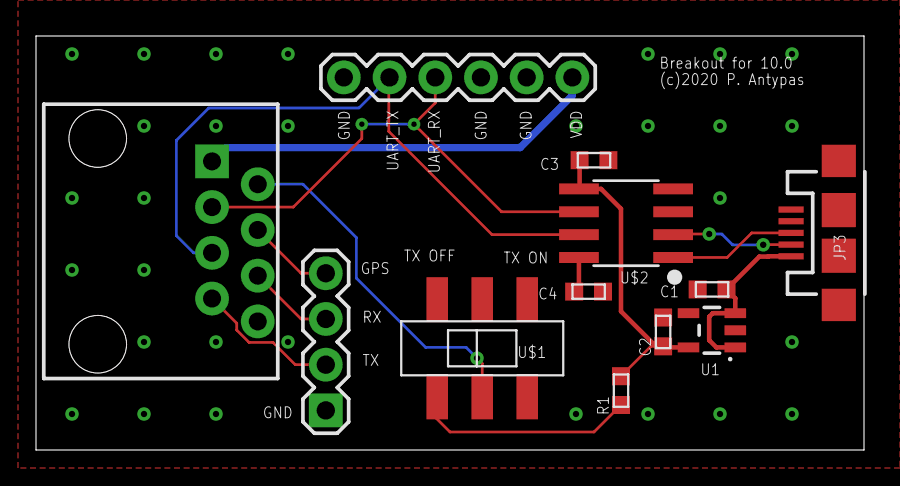
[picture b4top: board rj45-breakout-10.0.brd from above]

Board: 2 copper layers, 46.0 x 23.0 mm, 12 parts (0 on the bottom side), 14 nets.

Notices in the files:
eagle/fullcircuit4layer1.1b.brd:
(c) 2016 Peter Antypas
eagle/rf9.1.brd:
(c) 2016
latest/CAD/Board-10.0/rj45-breakout-10.0.brd:
(c)2020 P. Antypas
parts and their libraries:
SparkFun-Capacitors: Licensing: Creative Commons ShareAlike 4.0 International - https://creativecommons.org/licenses/by-sa/4.0
COPYRIGHT: Copyright (C) 2018 Accelerated Designs. All rights reserved
